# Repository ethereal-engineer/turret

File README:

An Arduino based, Portal themed, motion activated night light.

Schematic and PCB designed using KiCAD.

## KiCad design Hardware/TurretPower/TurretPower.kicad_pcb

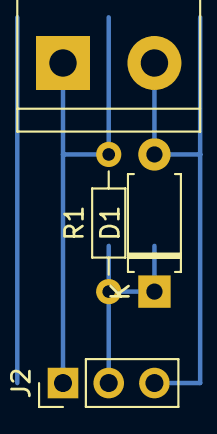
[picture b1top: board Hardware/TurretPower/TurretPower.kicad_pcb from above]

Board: 2 copper layers, 4 parts (0 on the bottom side), 3 nets.

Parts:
D1: 3V3; D_A-405_P7.62mm_Horizontal
J1: 5V1_Power_In; TerminalBlock_bornier-2_P5.08mm
J2: 3_Way_Power_Out; PinHeader_1x03_P2.54mm_Vertical
R1: 22; R_Axial_DIN0204_L3.6mm_D1.6mm_P7.62mm_Horizontal

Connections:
/3V3_Power_Out: D1.1, J2.2, R1.1
/5V1_In: J1.1, J2.1, R1.2
/GND: D1.2, J1.2, J2.3

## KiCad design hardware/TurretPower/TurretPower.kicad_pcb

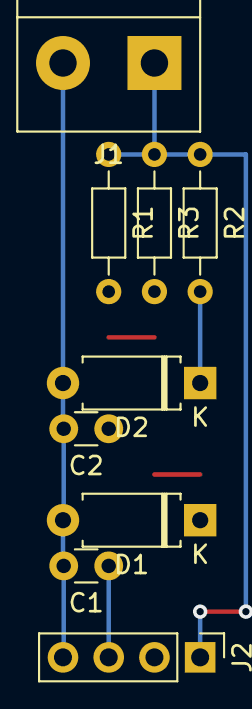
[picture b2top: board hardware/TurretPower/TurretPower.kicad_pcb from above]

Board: 2 copper layers, 9 parts (0 on the bottom side), 4 nets.

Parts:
C1, C2: 0.1uF; C_Disc_D3.0mm_W1.6mm_P2.50mm
D1: 3V3; D_A-405_P7.62mm_Horizontal
D2: 5V1; D_A-405_P7.62mm_Horizontal
J1: 5V1_Power_In; TerminalBlock_bornier-2_P5.08mm
J2: 3_Way_Power_Out; PinHeader_1x04_P2.54mm_Vertical
R1: 22; R_Axial_DIN0204_L3.6mm_D1.6mm_P7.62mm_Horizontal
R2, R3: 10; R_Axial_DIN0204_L3.6mm_D1.6mm_P7.62mm_Horizontal

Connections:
/3V3_80mA_Regulated_Out: C1.1, D1.1, J2.3, R1.2
/5V1_200mA_Regulated_Out: C2.1, D2.1, J2.2, R2.2, R3.2
/5V1_In: J1.1, J2.1, R1.1, R2.1, R3.1
/GND: C1.2, C2.2, D1.2, D2.2, J1.2, J2.4

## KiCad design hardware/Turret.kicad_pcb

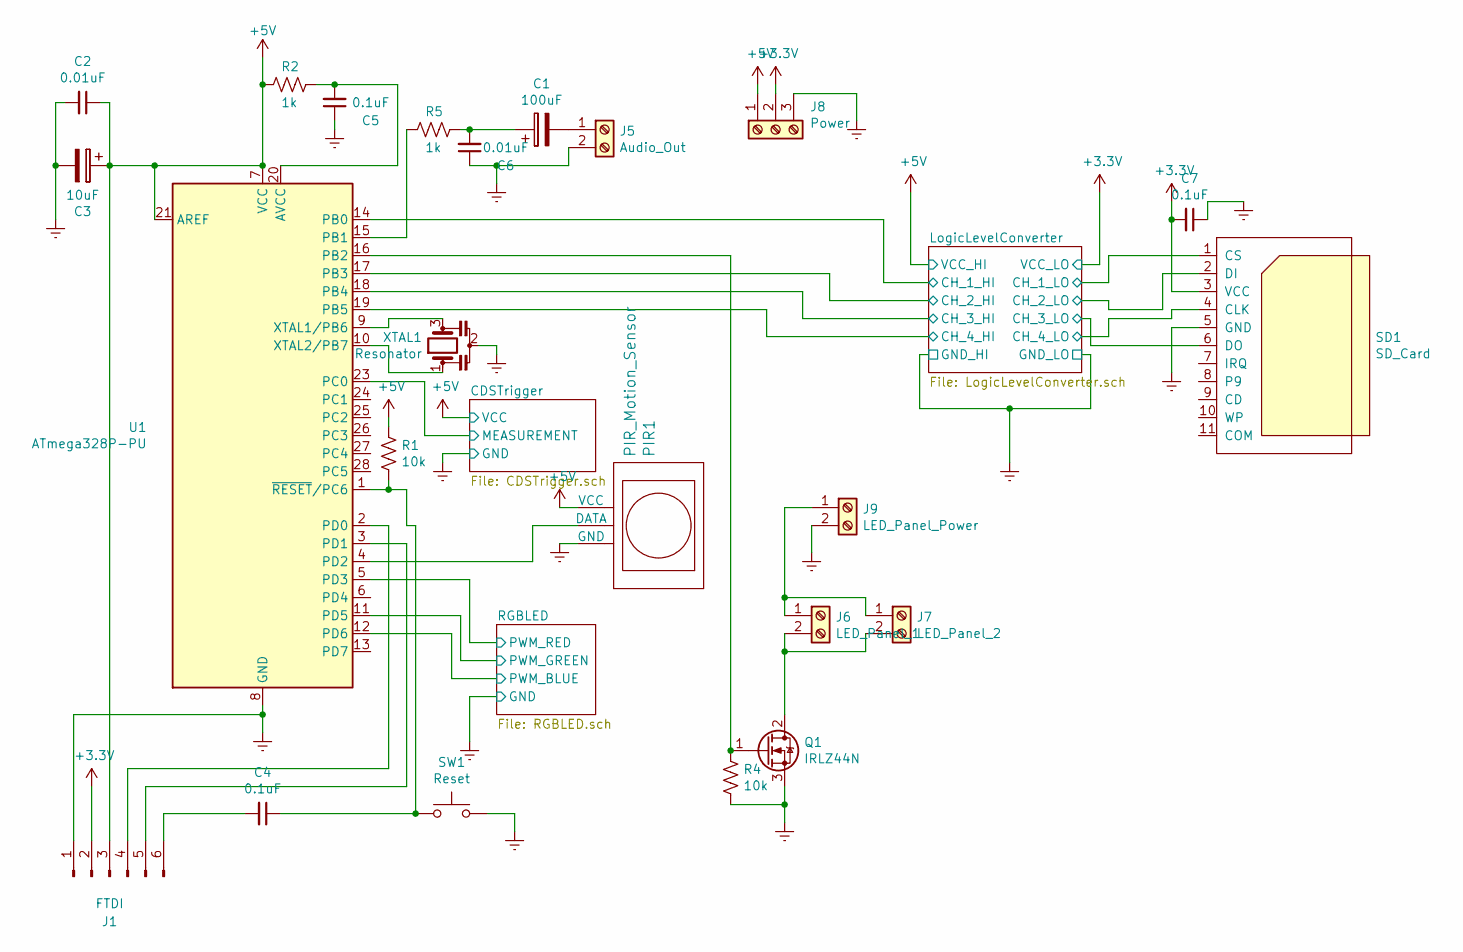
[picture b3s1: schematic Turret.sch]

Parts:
C1: 100uF; CP_Radial_D5.0mm_P2.50mm
C2, C6: 0.01uF; C_Disc_D3.0mm_W1.6mm_P2.50mm
C3: 10uF; CP_Radial_D5.0mm_P2.50mm
C4: 0.1uF; C_Disc_D7.5mm_W5.0mm_P7.50mm
C5, C7: 0.1uF; C_Disc_D3.0mm_W1.6mm_P2.50mm
J1: FTDI; PinHeader_1x06_P2.54mm_Vertical
J5: Audio_Out; TerminalBlock_bornier-2_P5.08mm
J6: LED_Panel_1; TerminalBlock_bornier-2_P5.08mm
J7: LED_Panel_2; TerminalBlock_bornier-2_P5.08mm
J8: Power; TerminalBlock_bornier-3_P5.08mm
J9: LED_Panel_Power; TerminalBlock_bornier-2_P5.08mm
PIR1: PIR_Motion_Sensor; PinHeader_1x03_P2.54mm_Vertical
Q1: IRLZ44N; TO-220-3_Vertical
R1, R4: 10k; R_Axial_DIN0204_L3.6mm_D1.6mm_P7.62mm_Horizontal
R2, R5: 1k; R_Axial_DIN0204_L3.6mm_D1.6mm_P7.62mm_Horizontal
SD1: SD_Card; SD_CARD_Breakout
SW1: Reset; SW_PUSH_6mm
U1: ATmega328P-PU; DIP-28_W7.62mm
XTAL1: Resonator; PinHeader_1x03_P2.54mm_Vertical

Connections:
/CDSTrigger/MEASUREMENT: U1.23 (PC0); also elsewhere on the board
/LogicLevelConverter/CH_1_HI: U1.14 (PB0); also elsewhere on the board
/LogicLevelConverter/CH_1_LO: SD1.1 (CS); also elsewhere on the board
/LogicLevelConverter/CH_2_HI: U1.17 (PB3); also elsewhere on the board
/LogicLevelConverter/CH_2_LO: SD1.2 (DI); also elsewhere on the board
/LogicLevelConverter/CH_3_HI: U1.18 (PB4); also elsewhere on the board
/LogicLevelConverter/CH_3_LO: SD1.6 (DO); also elsewhere on the board
/LogicLevelConverter/CH_4_HI: U1.19 (PB5); also elsewhere on the board
/LogicLevelConverter/CH_4_LO: SD1.4 (CLK); also elsewhere on the board
/RGBLED/PWM_BLUE: U1.12 (PD6); also elsewhere on the board
/RGBLED/PWM_GREEN: U1.11 (PD5); also elsewhere on the board
/RGBLED/PWM_RED: U1.5 (PD3); also elsewhere on the board
Earth: C2.2, C3.2, C5.1, C6.1, C7.1, J1.1, J5.2, J8.3, J9.2, PIR1.1 (GND), Q1.3 (S), R4.2, SD1.5 (GND), SW1.2, U1.8 (GND), U1.22 (GND), XTAL1.2; also elsewhere on the board
unnamed: C1.1, C6.2, R5.1
unnamed: C1.2, J5.1
unnamed: C4.1, R1.2, SW1.1, U1.1 (~RESET~/PC6)
unnamed: C4.2, J1.6
unnamed: C5.2, R2.1, U1.20 (AVCC)
unnamed: J1.4, U1.2 (PD0)
unnamed: J1.5, U1.3 (PD1)
unnamed: J6.1, J7.1, J9.1
unnamed: J6.2, J7.2, Q1.2 (D)
unnamed: PIR1.2 (DATA), U1.4 (PD2)
unnamed: Q1.1 (G), R4.1, U1.16 (PB2)
unnamed: R5.2, U1.15 (PB1)
unnamed: U1.9 (XTAL1/PB6), XTAL1.3
unnamed: U1.10 (XTAL2/PB7), XTAL1.1

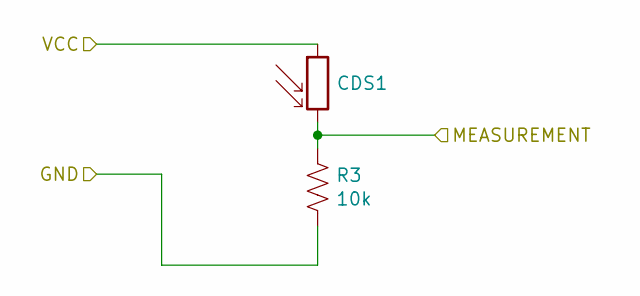
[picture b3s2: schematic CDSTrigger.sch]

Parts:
CDS1: ?; R_LDR_4.9x4.2mm_P2.54mm_Vertical
R3: 10k; R_Axial_DIN0204_L3.6mm_D1.6mm_P7.62mm_Horizontal

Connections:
/CDSTrigger/MEASUREMENT: CDS1.2, R3.1; also elsewhere on the board
Earth: R3.2; also elsewhere on the board

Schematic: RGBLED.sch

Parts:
J4: RGBLED_Input; PinHeader_1x04_P2.54mm_Vertical
U3: WS2811; DIP-8_W7.62mm_SMDSocket_SmallPads

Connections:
/RGBLED/PWM_BLUE: J4.3; also elsewhere on the board
/RGBLED/PWM_GREEN: J4.2; also elsewhere on the board
/RGBLED/PWM_RED: J4.1; also elsewhere on the board
Earth: J4.4; also elsewhere on the board

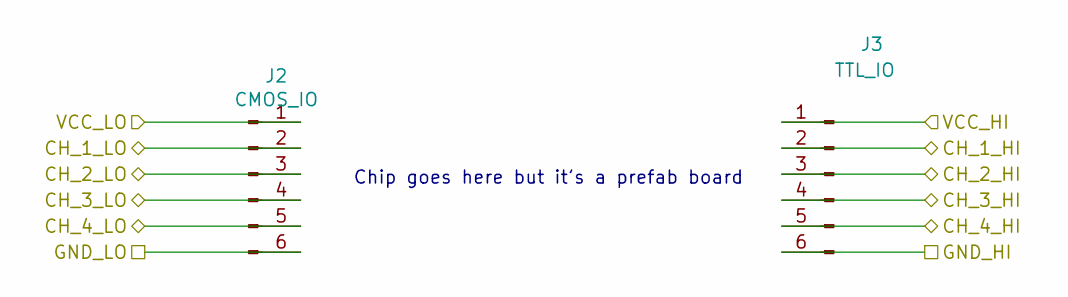
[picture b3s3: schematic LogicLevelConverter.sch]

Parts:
J2: CMOS_IO; PinSocket_1x06_P2.54mm_Vertical
J3: TTL_IO; PinSocket_1x06_P2.54mm_Vertical

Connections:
/LogicLevelConverter/CH_1_HI: J3.2; also elsewhere on the board
/LogicLevelConverter/CH_1_LO: J2.2; also elsewhere on the board
/LogicLevelConverter/CH_2_HI: J3.3; also elsewhere on the board
/LogicLevelConverter/CH_2_LO: J2.3; also elsewhere on the board
/LogicLevelConverter/CH_3_HI: J3.4; also elsewhere on the board
/LogicLevelConverter/CH_3_LO: J2.4; also elsewhere on the board
/LogicLevelConverter/CH_4_HI: J3.5; also elsewhere on the board
/LogicLevelConverter/CH_4_LO: J2.5; also elsewhere on the board
Earth: J2.6, J3.6; also elsewhere on the board

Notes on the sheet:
Chip goes here but it's a prefab board

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
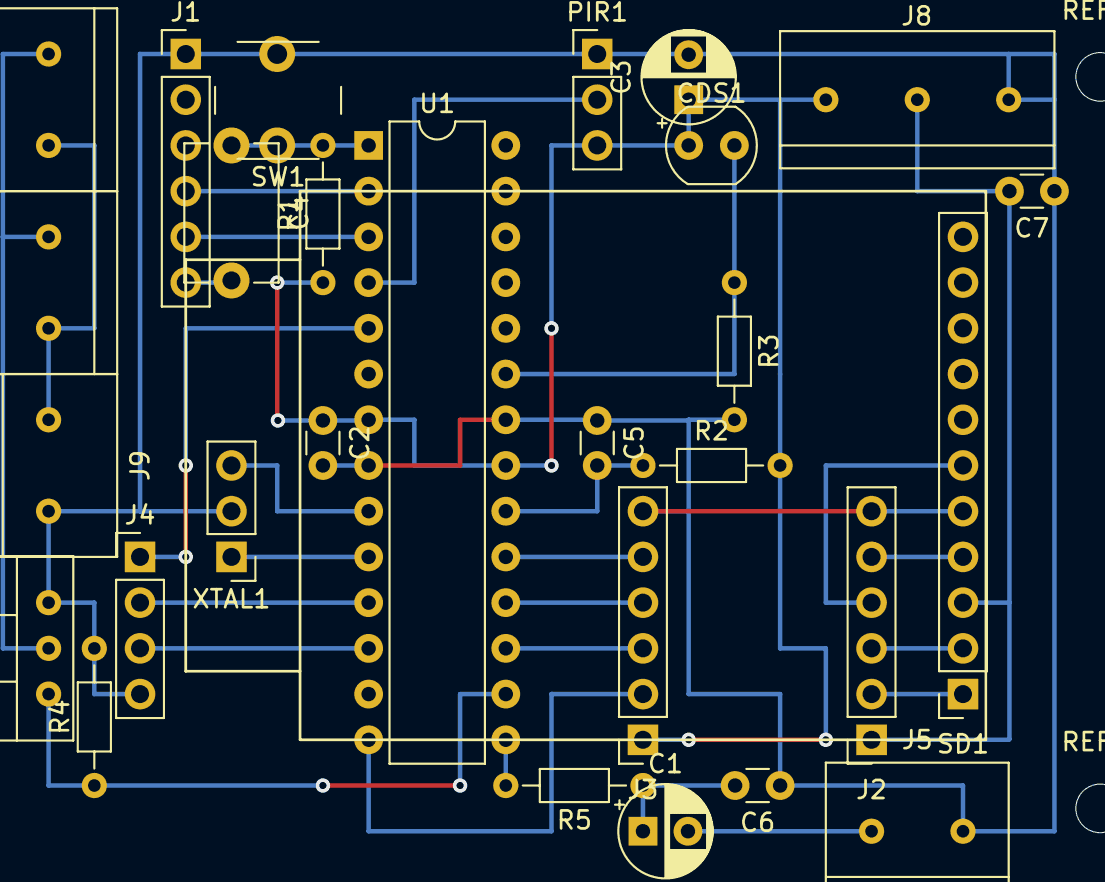
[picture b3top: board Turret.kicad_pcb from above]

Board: 2 copper layers, 28 parts (0 on the bottom side), 29 nets.

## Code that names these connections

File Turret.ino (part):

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
// RGB LED Eye

#define PIN_PWM_RED   3       // Physical Pin 5
#define PIN_PWM_GREEN 5       // Physical Pin 11
#define PIN_PWM_BLUE  6       // Physical Pin 12

// Speaker

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  // Debugging
  Serial.begin(9600);
  // Configure "THE EYE"
  eye.begin(PIN_PWM_RED, PIN_PWM_GREEN, PIN_PWM_BLUE);
  // Configure audio output
  audio.speakerPin = PIN_AUDIO_OUT; // PWM output is pin 9 for a UNO
  audio.quality(1);   
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
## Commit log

2018-10-19 Added short description
2018-10-19 First full day of work on Arduino code. Code complete, untested. Done in the car on the way down to Braidwood for Grandparents Day. I wrote my first class (for years) and I am really happy with the q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
2018-10-19 Added hardware files, shuffled directories
2018-10-19 Arduino IDE complained about the directory structure so I shuffled it again.
2018-10-20 Currently working on fixing the char/string issues. Almost there.
2018-10-20 I think all the bugs with PROGMEM use and strings are fixed...
2018-10-20 Pre-breadboard fixes * Added serial debug inputs m, d, and n for simulating motion, daylight, and low light, respectively. * Fixed incorrect 8.3 format AUTOSEARCH sound path * Added DEPLOY sounds to 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
2018-10-21 Converted schematic for standalone implementation * Boy that was more work than I wanted it to be! * Added physical pin comments to .ino file to help with wiring the schematic * Created an SD_CARD_11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
2018-10-22 Debugged and fine-tuned with breadboarded circuit * Added "debug settings panel" for debugging options * Added a space between logged variables * Added main loop delay define as 500ms * Added SECS_TO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
2018-10-22 Sound file addition * Added "Whoa" sound for when operation mode changes * Should I add sound files to the repo...? Gut says no.
2018-10-25 Removed .bck files from repo
    Just noticed yet another kind of bak file. Added
    it to .gitignore and removed it.
2018-10-25 A little more progress towards the vero-level PCB * Broke out the Logic Level Converter board and others to a seperate schematic file, using pin headers. I'm not really sure of the right way to do th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
2018-10-26 Hours spent getting the first vero-compatible trace * First draft is done. It is modestly elegant but can be improved. Next step now that positioning, alignment, wiring optimisation, and trace-cuttin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
2018-10-27 Added pull-down 10k resistor for mosfet
2018-10-29 Project updated to newer file version and fixed clk/din RGBLED mix up
2018-10-30 Some changes * Added screw terminals for external board connections like lights, audio, and now, power. * Removed 3.3v Zener (shithouse) regulator. I'll be creating a new sub-project that will supply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
2018-11-02 Removing noise, improving sound. Debugging... * Short timeouts are currently enabled for testing * Changed sleep mode eye colour to dim version to test PWM noise * Reinstated dimming of lights when s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
2018-11-03 From WS-chip to internal RGB PWM * Moved SD Card CS pin from 10(16) to 8(14) to allow PWM to be freed for light brightness control. * Moved from using an off-board RGBLED controller to using the ATME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
2018-11-03 Aligning hardware with breadboard part 1 * I've started updating the schematic from the changes made whilst breadboarding the entire device (again). Only two things remain. They are noted in text ON 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
2018-11-03 Added capacitors, low pass filters, and footprints... * Added schematic objects - need verification of value and proper wiring * Assigned footprints * Got started on the PCB
2018-11-04 Finished initial PCB... only to find it too large. * Probably what I should have done first. Hmmm. * Committing before resizing or redoing on non-vero dot-board (that just arrived the other day in th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
2018-11-04 Squished it all (PCB) into the new dot-board factor! * With relative ease (so far - no wiring yet) * Blue measurements are the limits of the enclosure * White measurements correspond to the available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
2018-11-04 Efforts towards a smaller PCB continue... * Removed the LLC chip (it's an external board anyway) * Most of PCB now routed * Updated schematic footprints so that they mesh with the PCB
2018-11-06 Just ONE ground/earth trace left to route and it's taking forever * All other PCB traces have been run * Power has been removed from the programming header, so now it must be externally powered even 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
2018-11-06 Started laying things out in the real world * Screw holes are something I didn't take into consideration when placing terminals, but I have worked around that by using flat screws in certain places. 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
2018-11-06 Removed ground from one of the Atmega pins as unneeded
2018-11-07 Dot-board PCB completed * Linked the missing trace * Tidied mess * Reduced wire traces to 5 * Now let's build this thing
2018-11-07 Added grid lines for build job
2018-11-07 Minor changes during physical placement * Moved grid to user comments layer and disabled for now * Moved 10uF cap out from under the SD card shadow because I could. It saves hassle tomorrow. Straight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
2018-11-12 Started (and mostly completed) power supply * Schematic is done (adjusted for available bits) * PCB is nearly done (in Vero style)
2018-11-13 Finished (and simplified) power supply board * I have built it, but I made it mirrored by mistake. No issues, though.
2018-11-18 Restored general use timeouts * Adjusted to taste
2018-12-25 Updated active timing
2019-06-02 Reverted to prior light timings
2020-09-20 Doing SOMETHING to get Turret fixes started
2020-09-20 Shuffled around so it builds at least. TBC
2020-09-24 Fiddling * Removed main loop delay - pointless in this context * Added some comments
2020-09-26 Removed duplicate hardware folder
2020-09-26 Turret's original personality has returned!
2020-09-26 Improved night/day hysterisis
